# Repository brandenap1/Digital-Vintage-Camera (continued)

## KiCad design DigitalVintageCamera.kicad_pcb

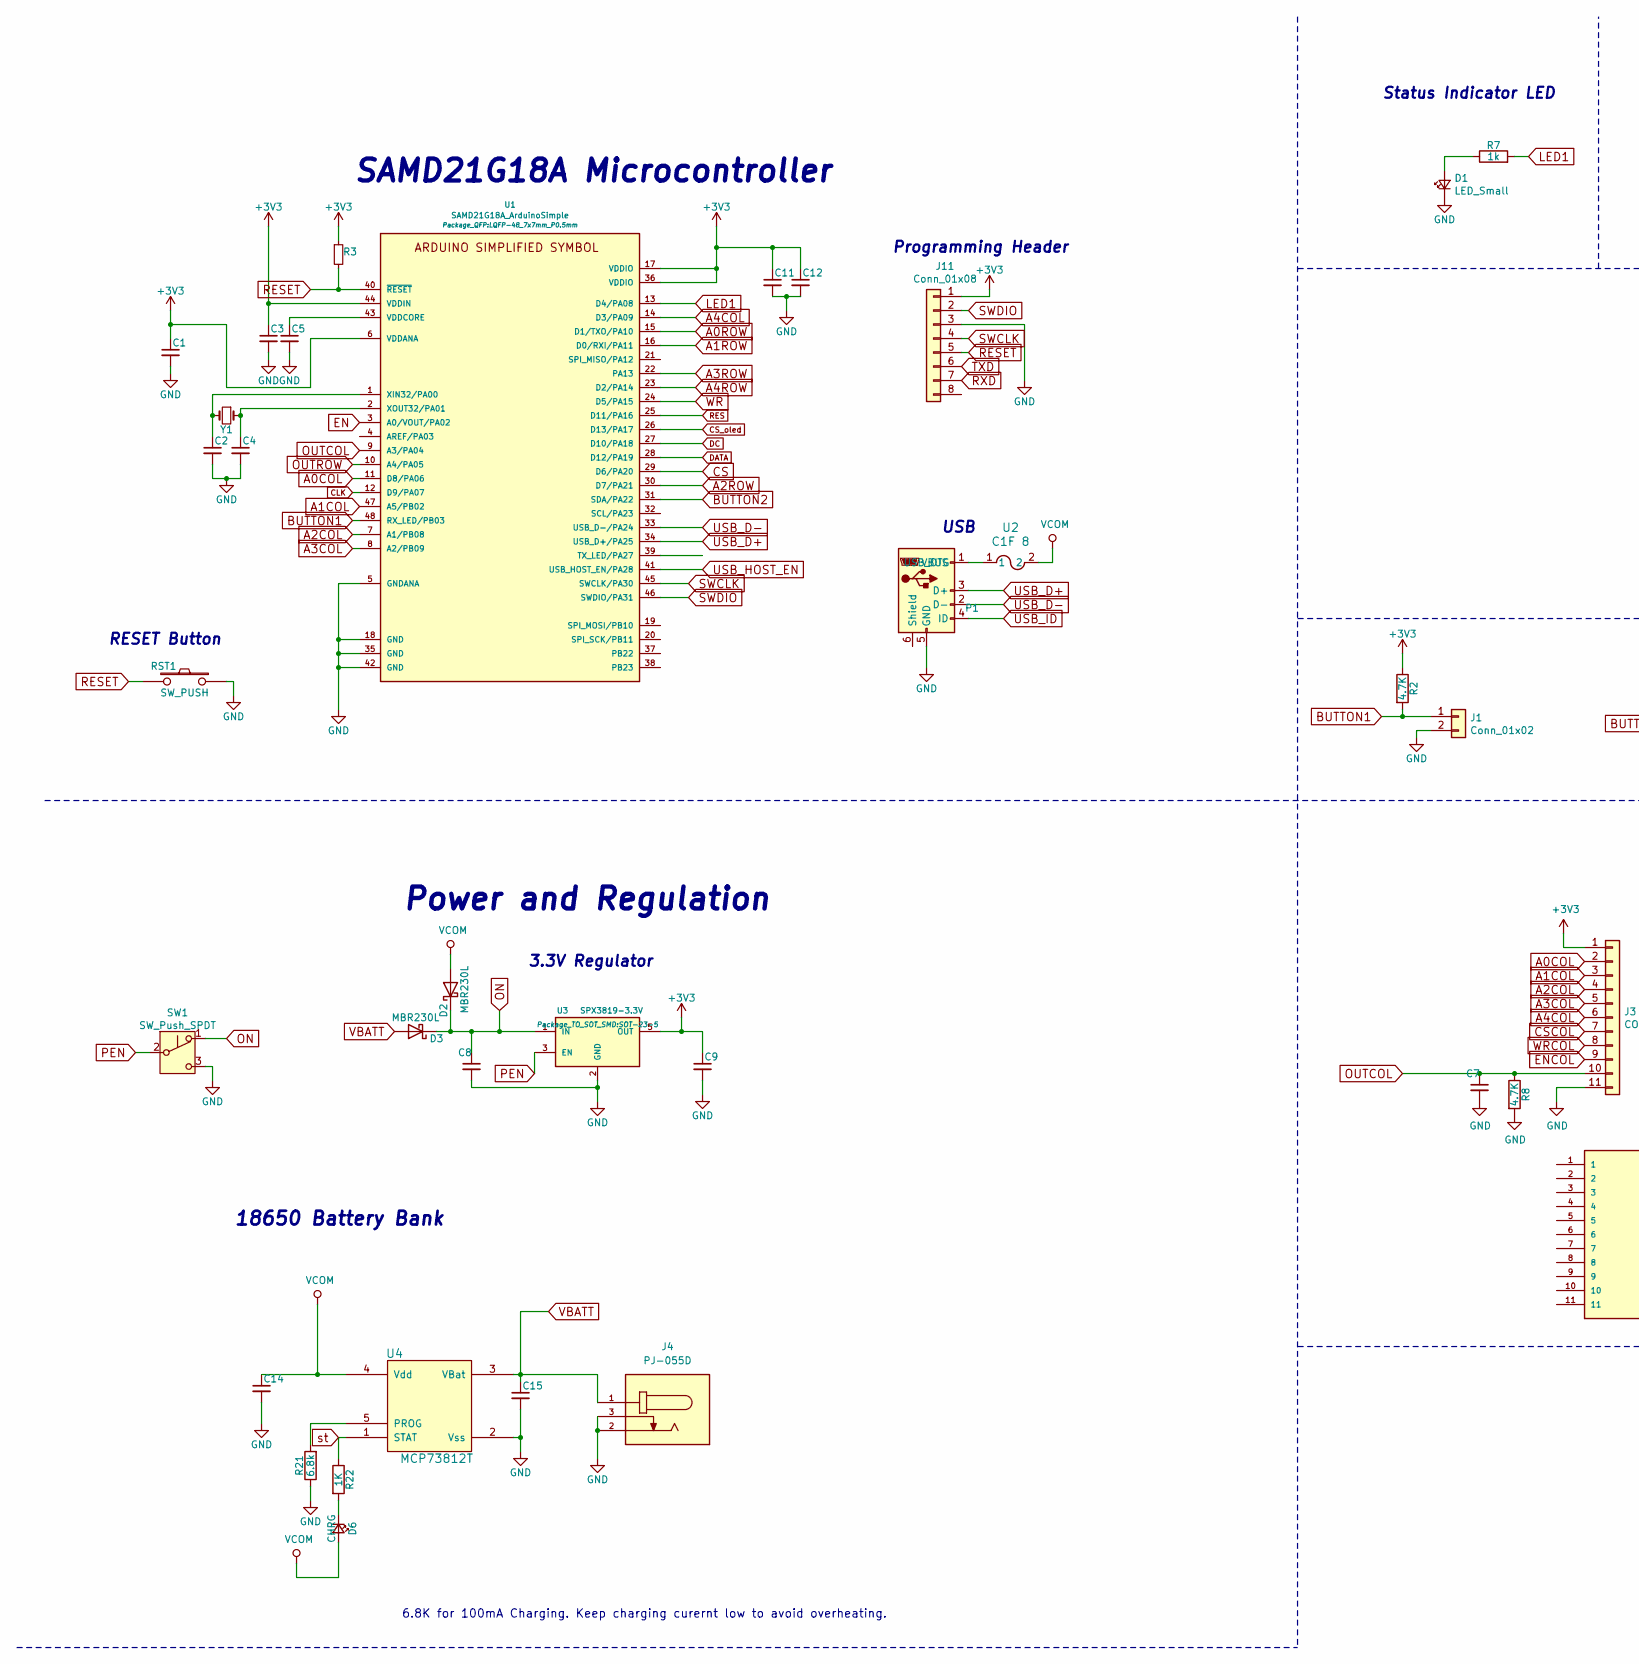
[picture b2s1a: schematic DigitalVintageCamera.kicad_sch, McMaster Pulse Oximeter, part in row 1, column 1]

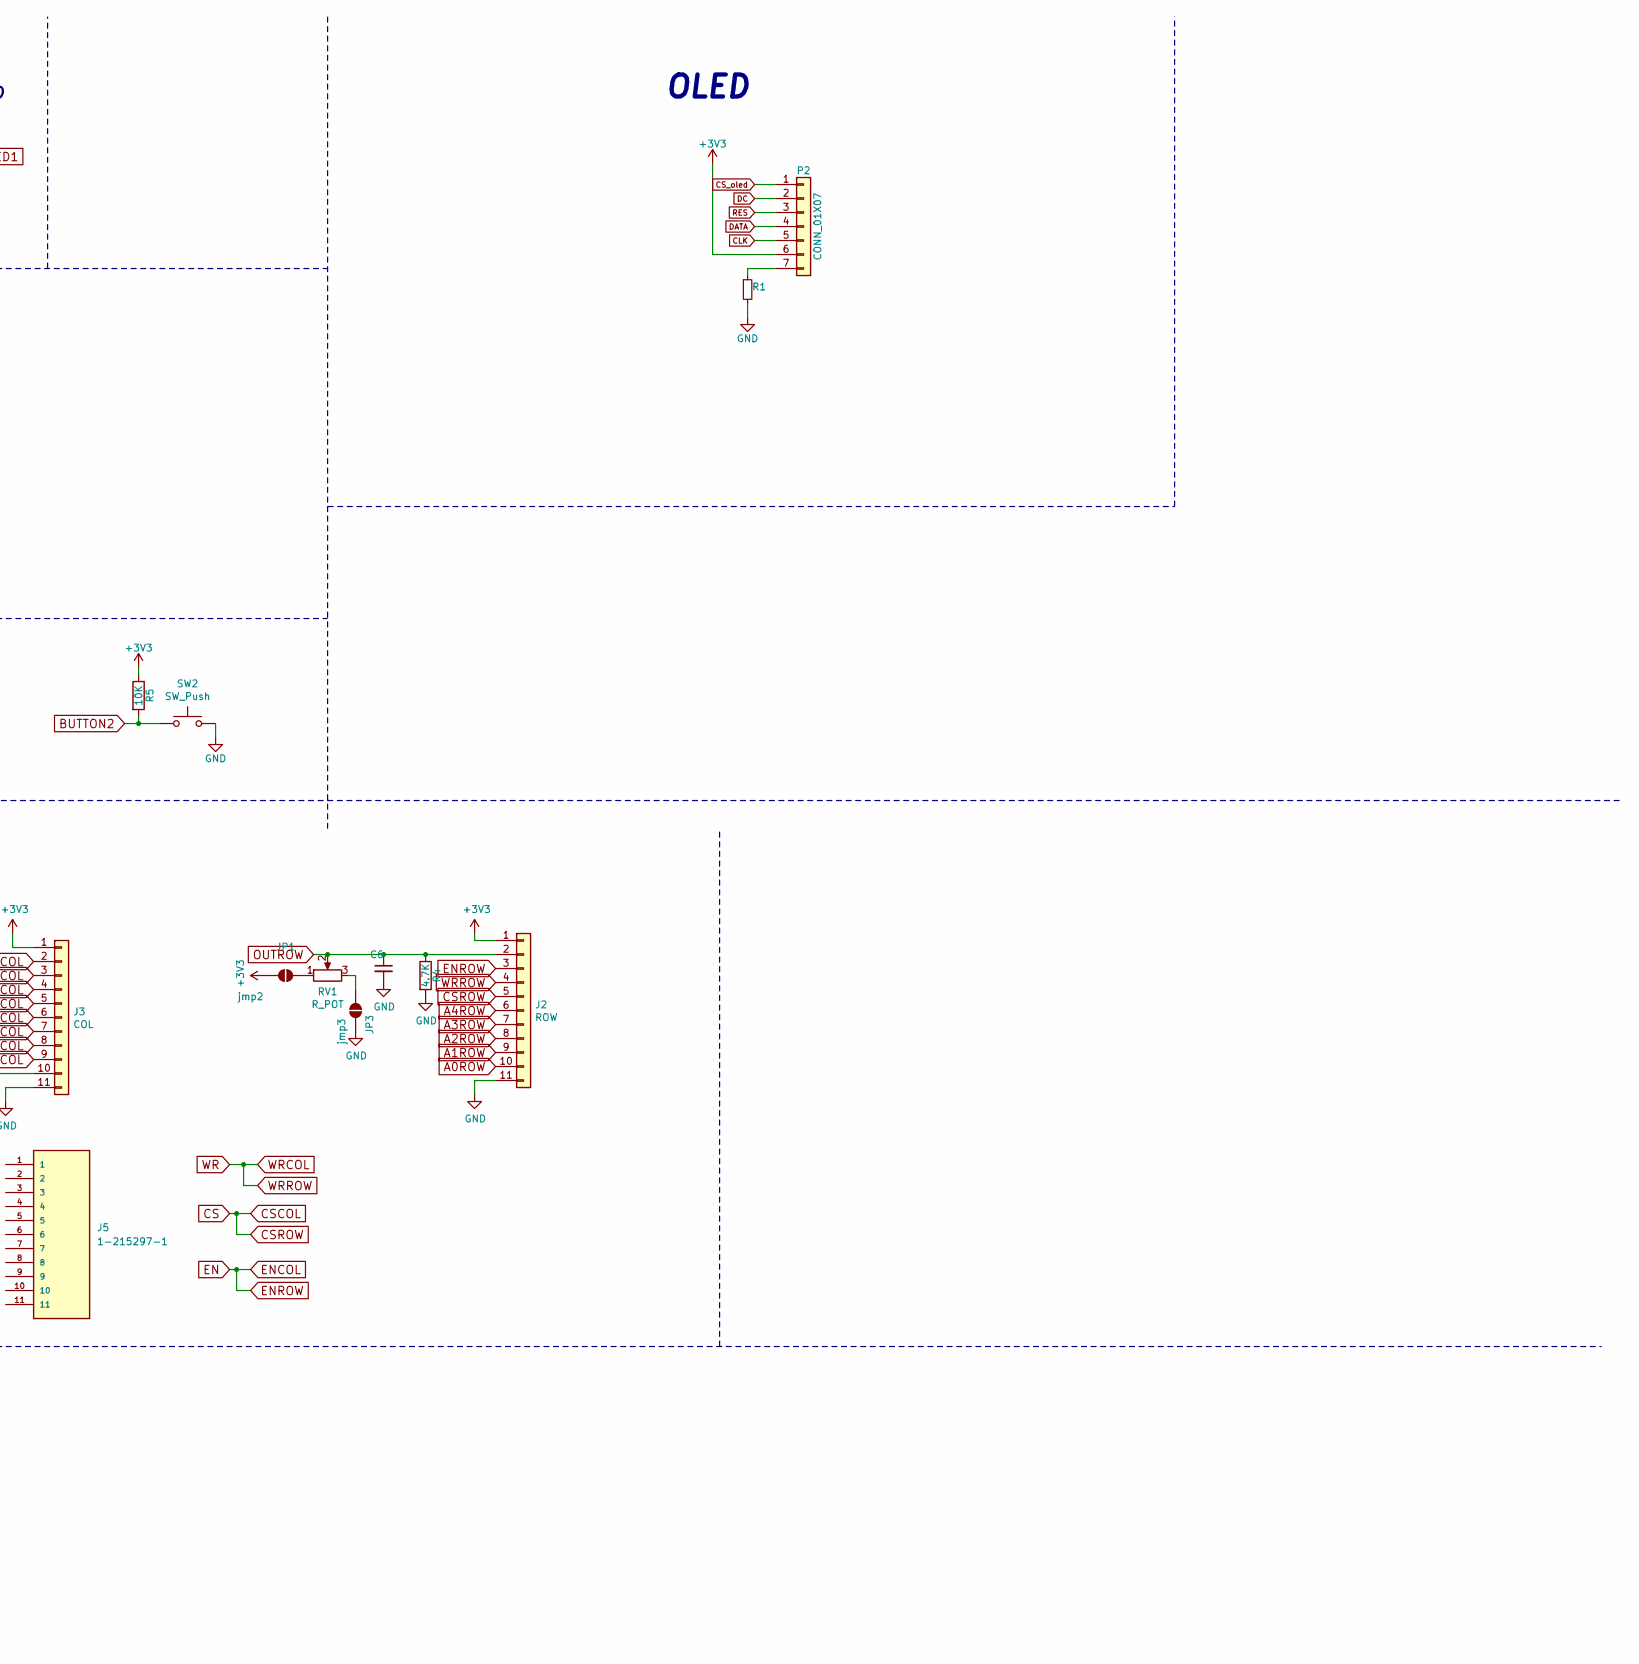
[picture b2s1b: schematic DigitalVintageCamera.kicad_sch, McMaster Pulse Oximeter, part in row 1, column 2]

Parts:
C1, C3, C5, C11, C12: 0.1uF; C_0805_2012Metric
C2, C4: 22pF; C_0805_2012Metric
C6, C7, C8: 1uF; C_0805_2012Metric
C9: 2.2uF; C_0805_2012Metric
C14, C15: 4.7uF; C_0805_2012Metric
D1: LED_Small; LED_0603_1608Metric
D2, D3: MBR230L; D_SOD-123F
D6: CHRG; LED_0805_2012Metric
J1: Conn_01x02; JST_PH_S2B-PH-K_1x02_P2.00mm_Horizontal
J2: ROW; PinSocket_1x11_P2.54mm_Vertical
J3: COL; PinSocket_1x11_P2.54mm_Vertical
J4: PJ-055D; CUI_PJ-055D; PARTREV 1.04
J5: 1-215297-1; TE_1-215297-1; PARTREV R
J11: Conn_01x08; PinSocket_1x08_P2.54mm_Vertical
JP1: jmp2; SolderJumper-2_P1.3mm_Open_RoundedPad1.0x1.5mm
JP3: jmp3; SolderJumper-2_P1.3mm_Open_RoundedPad1.0x1.5mm
P1: USB_OTG; USB_Micro-B_Molex-105017-0001
P2: CONN_01X07; PinSocket_1x07_P2.54mm_Vertical
R1: 100k; R_0805_2012Metric
R2, R4, R8: 4.7K; R_0805_2012Metric
R3: 10k; R_0805_2012Metric
R5: 10K; R_0805_2012Metric
R7: 1k; R_0805_2012Metric
R21: 6.8k; R_0805_2012Metric
R22: 1K; R_0805_2012Metric
RST1: SW_PUSH; SW_SPST_B3U-1000P
RV1: R_POT; Potentiometer_Bourns_PTV09A-1_Single_Vertical
SW1: SW_Push_SPDT; SW_Slide_1P2T_CK_OS102011MS2Q
SW2: SW_Push; SW_SPST_EVPBF
U1: SAMD21G18A_ArduinoSimple; LQFP-48_7x7mm_P0.5mm
U2: C1F 8; C1_BEL
U3: SPX3819-3.3V; SOT-23-5
U4: MCP73812T; SOT-23-5
Y1: Crystal_Small; Crystal_SMD_3215-2Pin_3.2x1.5mm

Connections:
+3V3: C1.1, C3.1, C9.1, C11.1, C12.1, J2.1, J3.1, J11.1, JP1.1 (A), P2.6, R2.1, R3.1, R5.1, U1.6 (VDDANA), U1.17 (VDDIO), U1.36 (VDDIO), U1.44 (VDDIN), U3.5 (OUT)
A0COL: J3.2, U1.11 (D8/PA06)
A0ROW: J2.10, U1.15 (D1/TXO/PA10)
A1COL: J3.3, U1.47 (A5/PB02)
A1ROW: J2.9, U1.16 (D0/RXI/PA11)
A2COL: J3.4, U1.7 (A1/PB08)
A2ROW: J2.8, U1.30 (D7/PA21)
A3COL: J3.5, U1.8 (A2/PB09)
A3ROW: J2.7, U1.22 (PA13)
A4COL: J3.6, U1.14 (D3/PA09)
A4ROW: J2.6, U1.23 (D2/PA14)
BUTTON1: J1.1, R2.2, U1.48 (RX_LED/PB03)
BUTTON2: R5.2, SW2.1, U1.31 (SDA/PA22)
CLK: P2.5, U1.12 (D9/PA07)
CS: J2.5, J3.7, U1.29 (D6/PA20)
CS_oled: P2.1, U1.26 (D13/PA17)
DATA: P2.4, U1.28 (D12/PA19)
DC: P2.2, U1.27 (D10/PA18)
EN: J2.3, J3.9, U1.3 (A0/VOUT/PA02)
GND: C1.2, C2.2, C3.2, C4.2, C5.2, C6.2, C7.2, C8.2, C9.2, C11.2, C12.2, C14.2, C15.2, D1.1 (K), J1.2, J2.11, J3.11, J4.2, J4.3, J11.3, JP3.2 (B), P1.5 (GND), R1.2, R4.2, R8.2, R21.1, RST1.1, SW1.3 (C), SW2.2, U1.5 (GNDANA), U1.18 (GND), U1.35 (GND), U1.42 (GND), U3.2 (GND), U4.2 (Vss)
LED1: R7.2, U1.13 (D4/PA08)
unnamed: D1.2 (A), R7.1
unnamed: D6.1 (K), R22.2
unnamed: JP1.2 (B), RV1.1
unnamed: JP3.1 (A), RV1.3
unnamed: P2.7, R1.1
unnamed: C5.1, U1.43 (VDDCORE)
unnamed: C2.1, U1.1 (XIN32/PA00), Y1.2
unnamed: C4.1, U1.2 (XOUT32/PA01), Y1.1
unnamed: R21.2, U4.5 (PROG)
ON: C8.1, D2.1 (K), D3.1 (K), SW1.1 (A), U3.1 (IN)
OUTCOL: C7.1, J3.10, R8.1, U1.9 (A3/PA04)
OUTROW: C6.1, J2.2, R4.1, RV1.2, U1.10 (A4/PA05)
PEN: SW1.2 (B), U3.3 (EN)
RES: P2.3, U1.25 (D11/PA16)
RESET: J11.5, R3.2, RST1.2, U1.40 (~RESET)
RXD: J11.7
SWCLK: J11.4, U1.45 (SWCLK/PA30)
SWDIO: J11.2, U1.46 (SWDIO/PA31)
TXD: J11.6
USB_D+: P1.3 (D+), U1.34 (USB_D+/PA25)
USB_D-: P1.2 (D-), U1.33 (USB_D-/PA24)
USB_HOST_EN: U1.41 (USB_HOST_EN/PA28)
USB_ID: P1.4 (ID)
VBATT: C15.1, D3.2 (A), J4.1, U4.3 (VBat)
VCOM: C14.1, D2.2 (A), D6.2 (A), U2.2, U4.4 (Vdd)
WR: J2.4, J3.8, U1.24 (D5/PA15)
st: R22.1, U4.1 (STAT)

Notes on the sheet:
Programming Header
6.8K for 100mA Charging. Keep charging curernt low to avoid overheating.
18650 Battery Bank
3.3V Regulator
SAMD21G18A Microcontroller
OLED
Status Indicator LED
USB
RESET Button
Power and Regulation

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
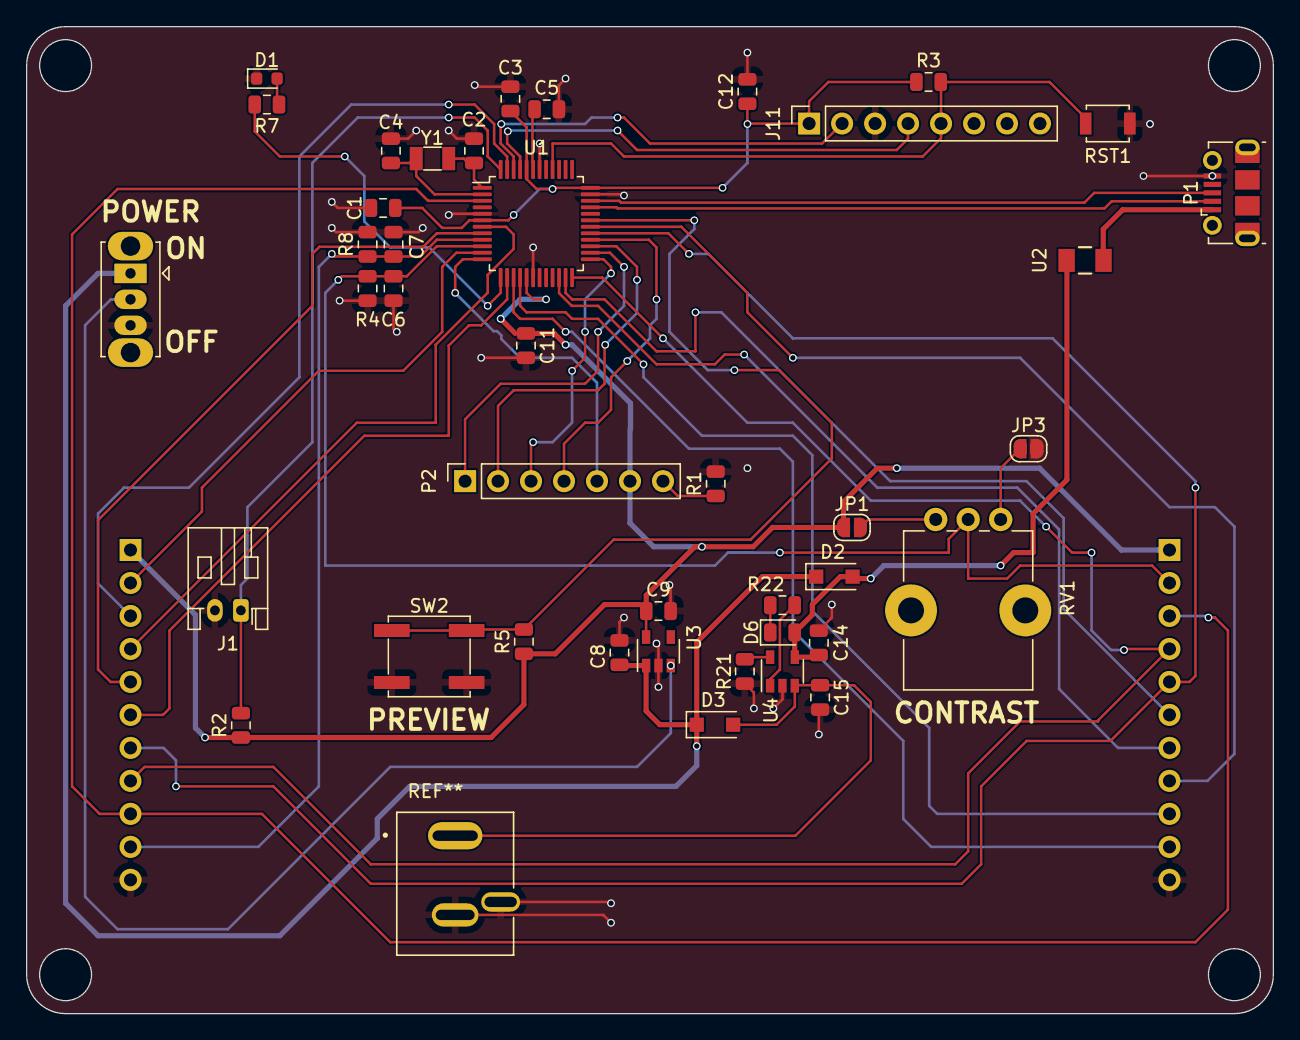
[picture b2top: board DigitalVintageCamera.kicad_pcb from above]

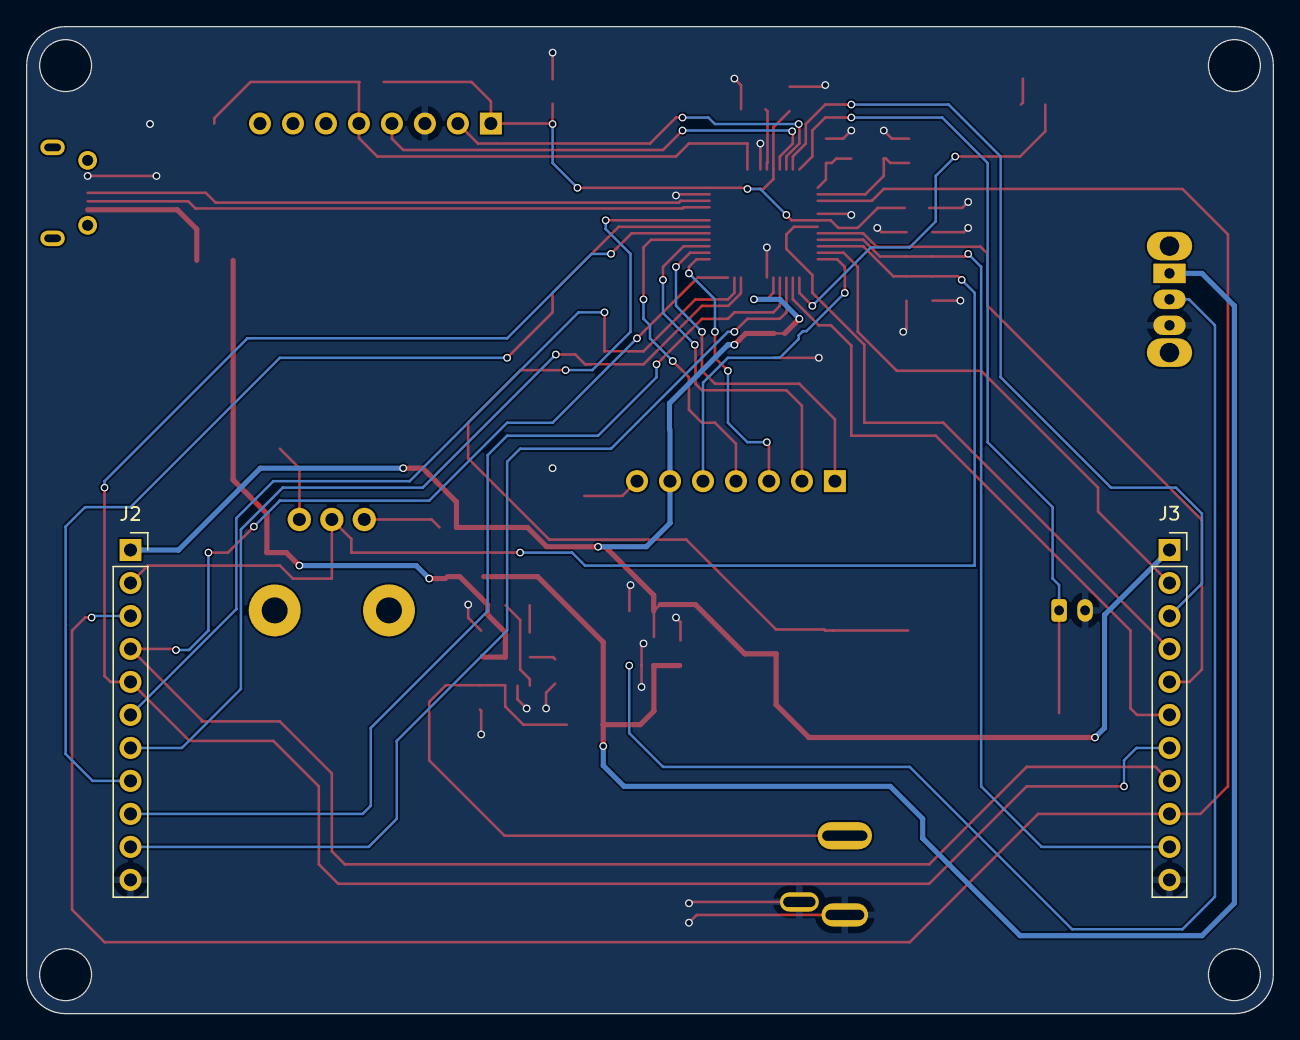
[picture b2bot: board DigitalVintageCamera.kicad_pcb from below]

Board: 2 copper layers, 96.0 x 76.0 mm, 43 parts (2 on the bottom side), 45 nets.

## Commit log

2024-09-20 Update README.md
    wrote intial description for readme
2024-09-20 Add files via upload
    Adding initial files (i.e. Firmware, PCB designs, and 3D models)
